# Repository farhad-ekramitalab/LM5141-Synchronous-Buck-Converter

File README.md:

# LM5141-Q1 Synchronous Buck Converter

## Project Overview

Design and implementation of a 12 V to 3.3 V, 5 A synchronous buck converter using the Texas Instruments LM5141-Q1 peak-current-mode controller.

This project covers the complete development flow:

- Power-stage design
- LTspice simulation
- Control-loop design
- Compensation design
- KiCad schematic capture
- 4-layer PCB layout
- Manufacturing preparation
- Hardware validation (in progress)

---
## 📄 Portfolio Report

A concise engineering portfolio summarizing the complete design workflow, including system specifications, LTspice simulations, control-loop design, PCB implementation, manufacturing, and engineering skills demonstrated throughout the project.

**Report:**

[`Docs/LM5141-Synchronous Buck Converter Report.pdf`](Docs/LM5141-Synchronous%20Buck%20Converter%20Report.pdf)

## Specifications

| Parameter | Value |
|------------|------------|
| Input Voltage | 8 V – 16 V |
| Nominal Input Voltage | 12 V |
| Output Voltage | 3.3 V |
| Output Current | 5 A |
| Switching Frequency | 440 kHz |
| Topology | Synchronous Buck |
| Controller | LM5141-Q1 |
| Control Method | Peak Current Mode |

---

## Design Highlights

- Peak current mode control
- Type-II compensation network
- Loop crossover frequency ≈ 37 kHz
- Phase margin ≈ 83°
- 4-layer PCB implementation
- Kelvin current sensing
- AGND / PGND separation
- Optimized switching-node layout

---

## Current Status

- [x] Power stage design completed
- [x] LTspice simulation completed
- [x] Compensation design completed
- [x] KiCad schematic completed
- [x] PCB layout completed
- [x] PCB ordered
- [ ] Assembly
- [ ] Hardware validation
- [ ] Efficiency characterization
- [ ] Thermal characterization
---

## Tools Used

- LTspice
- KiCad 9
- TI WEBENCH
- Oscilloscope (planned validation)

---

## 🔗 Additional Resources

* 📁 **KiCad Project:** `KiCad/`
* ⚡ **LTspice Simulations:** `LTspice/`
* 🖼️ **Project Images:** `Images/`
* 📦 **Bill of Materials (BOM):** `BOM/`
* 📄 **Portfolio Report:** `Docs/LM5141-Synchronous Buck Converter Report.pdf`

---

## Author

Farhad Ekramitalab

Hardware Engineer | Power Electronics | SMPS | PCB Design | LTspice

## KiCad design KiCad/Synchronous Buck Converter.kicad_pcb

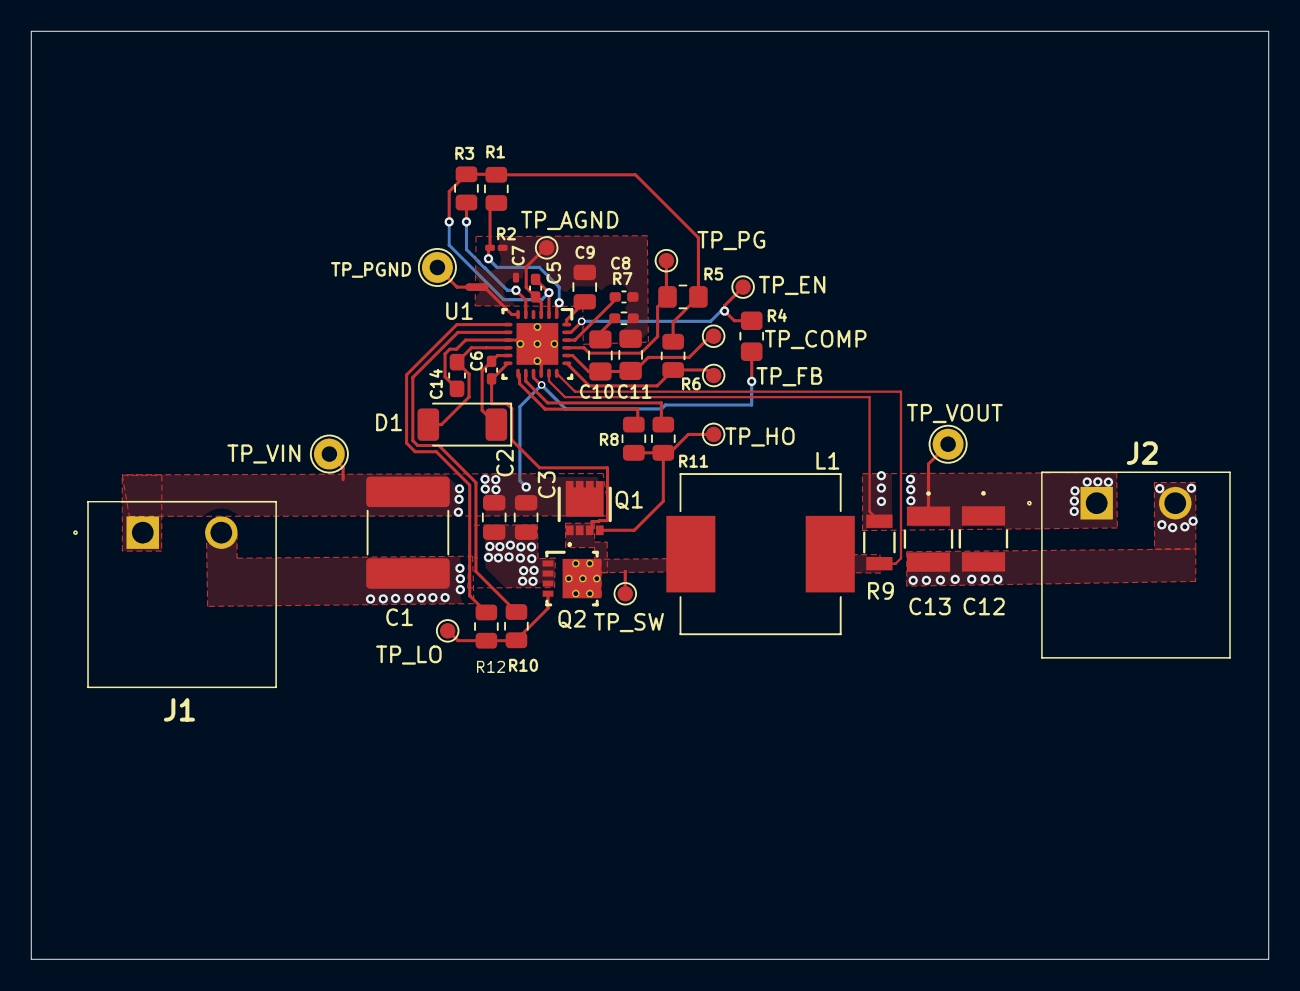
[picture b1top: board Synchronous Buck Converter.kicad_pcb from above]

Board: 4 copper layers, 80.0 x 60.0 mm, 44 parts (0 on the bottom side), 24 nets.

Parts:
C1: 47uF; C_2220_5750Metric_Pad1.97x5.40mm_HandSolder
C2: 10uF; C_0805_2012Metric
C3, C9: 100nF; C_0805_2012Metric
C5: 100nF; C_0402_1005Metric_Pad0.74x0.62mm_HandSolder
C6: 470nF; C_0402_1005Metric_Pad0.74x0.62mm_HandSolder
C7: DNP; C_0201_0603Metric_Pad0.64x0.40mm_HandSolder
C8: 47nF; C_0402_1005Metric_Pad0.74x0.62mm_HandSolder
C10: 22nF; C_0805_2012Metric_Pad1.18x1.45mm_HandSolder
C11: 180pF; C_0805_2012Metric_Pad1.18x1.45mm_HandSolder
C12, C13: 22uF; CAP_MSAS_32MS_TAY
C14: 2.2uF; C_0603_1608Metric_Pad1.08x0.95mm_HandSolder
D1: PMEG4050EP; D_SOD-128
J1: VIN_IN; 1757242
J2: VOUT_OUT; 1757242
L1: IHLP4040DZERR56M01; L_Vishay_IHLP-4040
NT1: NetTie_2; NetTie-2_SMD_Pad0.5mm
Q1: CSD17308Q3
Q2: CSD17577Q3A; DNH0008A
R1, R3, R6, R11, R12: 0; R_0805_2012Metric
R2: DNP; R_0201_0603Metric_Pad0.64x0.40mm_HandSolder
R4: 100k; R_0805_2012Metric_Pad1.20x1.40mm_HandSolder
R5: 10k; R_0805_2012Metric_Pad1.20x1.40mm_HandSolder
R7: 2.55k; R_0402_1005Metric_Pad0.72x0.64mm_HandSolder
R8, R10: 2.2; R_0805_2012Metric
R9: 10m; STA_CSR1206_STP
TP_AGND: TP_AGND; TestPoint_Pad_D1.0mm
TP_COMP: TP_COMP; TestPoint_Pad_D1.0mm
TP_EN: TP_EN; TestPoint_Pad_D1.0mm
TP_FB: TP_FB; TestPoint_Pad_D1.0mm
TP_HO: TP_HO; TestPoint_Pad_D1.0mm
TP_LO: TP_LO; TestPoint_Pad_D1.0mm
TP_PG: TP_PG; TestPoint_Pad_D1.0mm
TP_PGND: TP_PGND; TestPoint_THTPad_D2.0mm_Drill1.0mm
TP_SW: TP_SW; TestPoint_Pad_D1.0mm
TP_VIN: TP_VIN; TestPoint_THTPad_D2.0mm_Drill1.0mm
TP_VOUT: TP_VOUT; TestPoint_THTPad_D2.0mm_Drill1.0mm
U1: LM5141QRGERQ1; RGE0024H

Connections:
/COMP: C10.1, C11.1, TP_COMP.1, U1.20 (COMP)
/CS: L1.1, R9.1, U1.18 (CS)
/EN: R4.1, TP_EN.1, U1.23 (EN)
/FB: R6.1, TP_FB.1, U1.19 (FB)
/HB: C6.1, D1.1 (K), U1.11 (HB)
/PG: R5.1, TP_PG.1, U1.21 (PG)
/SW: C6.2, L1.2, Q1.1 (S_1), Q1.2 (S_2), Q1.3 (S_3), Q2.5 (D_1), Q2.6 (D_2), Q2.7 (D_3), Q2.8 (D_4), Q2.9, TP_SW.1, U1.12 (SW)
/VCC: C14.1, D1.2 (A), U1.10 (VCC)
/VDDA: C5.1, R1.2, R3.2, R5.2, R6.2, U1.2 (VDDA)
/VIN: C1.1, C2.1, C3.1, J1.1 (VIN), Q1.5 (D_1), Q1.6 (D_2), Q1.7 (D_3), Q1.8 (D_4), Q1.9 (D_5), R4.2, TP_VIN.1, U1.15 (VIN)
/VOUT: C12.1, C13.1, J2.1 (VIN), R9.2, TP_VOUT.1, U1.17 (VOUT)
AGND: C5.2, C7.2, C8.2, C9.2, C11.2, NT1.2, R2.1, R7.1, TP_AGND.1, U1.3 (AGND), U1.6 (OSC)
unnamed: C10.2, R7.2
unnamed: Q1.4 (G), R8.1, R11.1, TP_HO.1
unnamed: Q2.4 (G), R10.1, R12.1, TP_LO.1
unnamed: R1.1, R2.2, U1.1 (DEMB)
unnamed: C7.1, R3.1, U1.5 (DITH)
unnamed: R8.2, U1.13 (HO)
unnamed: R11.2, U1.14 (HOL)
unnamed: R12.2, U1.7 (LO)
unnamed: R10.2, U1.8 (LOL)
unnamed: C9.1, U1.24 (RES)
unnamed: C8.1, U1.22 (SS)
PGND: C1.2, C2.2, C3.2, C12.2, C13.2, C14.2, J1.2 (PGND), J2.2 (PGND), NT1.1, Q2.1 (S_1), Q2.2 (S_2), Q2.3 (S_3), TP_PGND.1, U1.9 (PGND), U1.16 (VCCX), U1.25 (DAP)

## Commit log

2026-06-23 Create LTSpice
2026-06-23 Create LTspice folder
2026-06-23 Create KiCad
2026-06-23 Rename AC Analysis Final.PNG to Bode Plot.PNG
2026-06-23 Create Images
2026-06-23 Create Gitkeep
2026-06-23 Create deletmelater
2026-06-23 Create delmela
2026-06-24 Create delmelater
2026-06-24 Create delemlater
